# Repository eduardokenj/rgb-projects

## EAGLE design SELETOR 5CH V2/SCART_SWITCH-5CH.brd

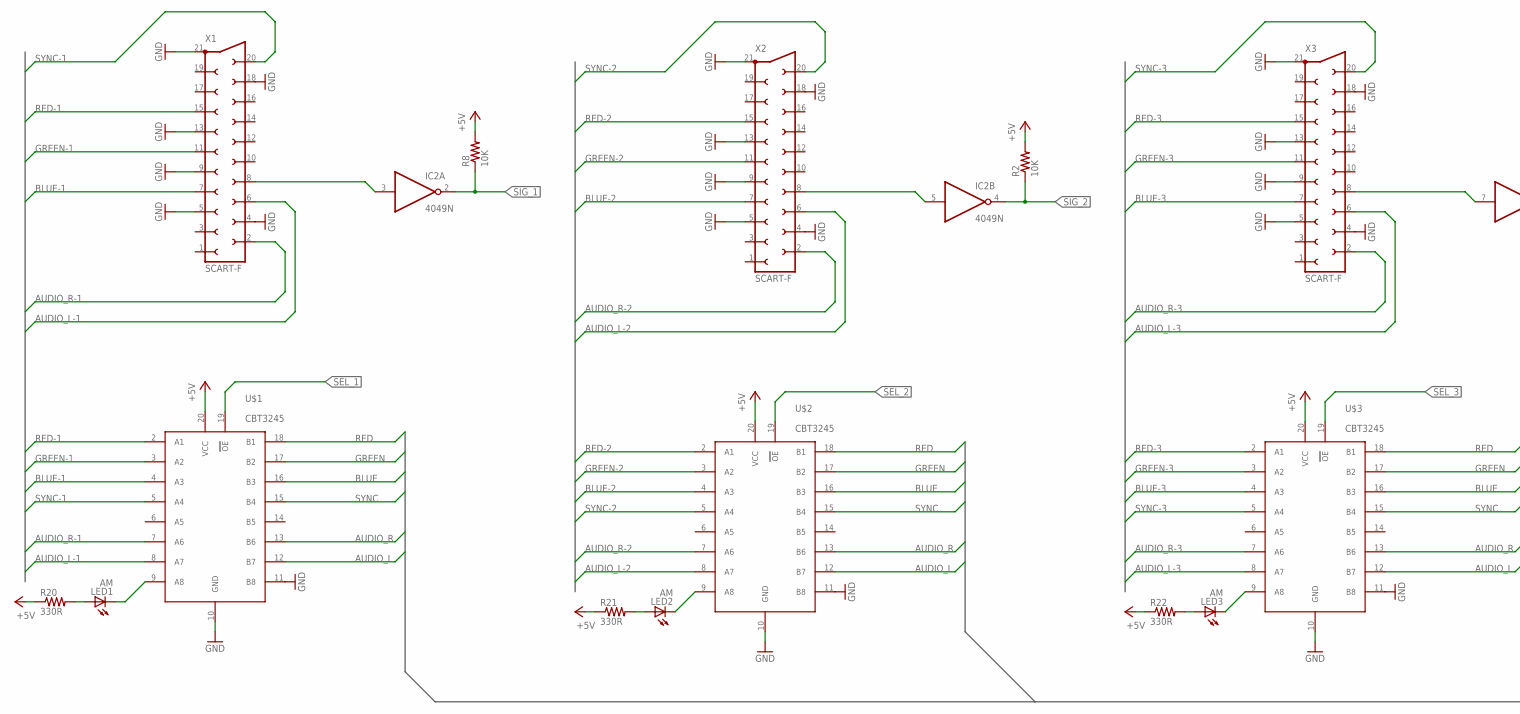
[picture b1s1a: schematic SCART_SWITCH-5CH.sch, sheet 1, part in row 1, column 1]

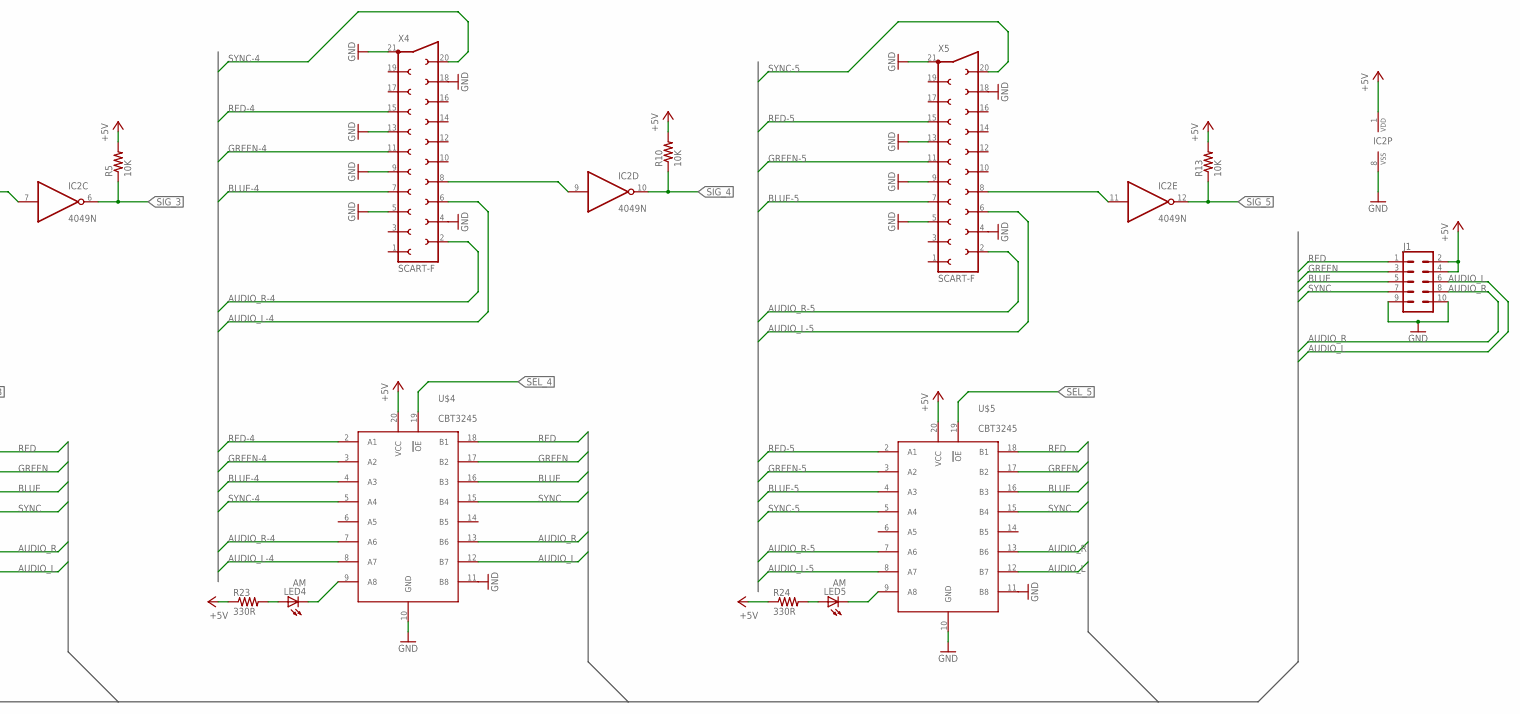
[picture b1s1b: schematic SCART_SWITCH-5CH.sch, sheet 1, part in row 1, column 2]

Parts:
IC2: 4049N; DIL16
J1: CONN_05X2SHD; 2X5-SHROUDED
LED1, LED2, LED3, LED4, LED5: AM; LED5MM
R2, R5, R8, R10, R13: 10K; 0204/7
R20, R21, R22, R23, R24: 330R; 0207/2V
U$1, U$2, U$3, U$4, U$5: CBT3245; SO20
X1, X2, X3, X4, X5: SCART-F

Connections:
+5V: IC2.1 (VDD), J1.2, J1.4, R2.2, R5.2, R8.2, R10.2, R13.2, R20.1, R21.1, R22.1, R23.1, R24.1, U$1.20 (VCC), U$2.20 (VCC), U$3.20 (VCC), U$4.20 (VCC), U$5.20 (VCC); also elsewhere on the board
AUDIO_L: J1.6, U$1.12 (B7), U$2.12 (B7), U$3.12 (B7), U$4.12 (B7), U$5.12 (B7)
AUDIO_L-1: U$1.8 (A7), X1.6
AUDIO_L-2: U$2.8 (A7), X2.6
AUDIO_L-3: U$3.8 (A7), X3.6
AUDIO_L-4: U$4.8 (A7), X4.6
AUDIO_L-5: U$5.8 (A7), X5.6
AUDIO_R: J1.8, U$1.13 (B6), U$2.13 (B6), U$3.13 (B6), U$4.13 (B6), U$5.13 (B6)
AUDIO_R-1: U$1.7 (A6), X1.2
AUDIO_R-2: U$2.7 (A6), X2.2
AUDIO_R-3: U$3.7 (A6), X3.2
AUDIO_R-4: U$4.7 (A6), X4.2
AUDIO_R-5: U$5.7 (A6), X5.2
BLUE: J1.5, U$1.16 (B3), U$2.16 (B3), U$3.16 (B3), U$4.16 (B3), U$5.16 (B3)
BLUE-1: U$1.4 (A3), X1.7
BLUE-2: U$2.4 (A3), X2.7
BLUE-3: U$3.4 (A3), X3.7
BLUE-4: U$4.4 (A3), X4.7
BLUE-5: U$5.4 (A3), X5.7
GND: IC2.8 (VSS), J1.9, J1.10, U$1.10 (GND), U$1.11 (B8), U$2.10 (GND), U$2.11 (B8), U$3.10 (GND), U$3.11 (B8), U$4.10 (GND), U$4.11 (B8), U$5.10 (GND), U$5.11 (B8), X1.4, X1.5, X1.9, X1.13, X1.18, X1.21, X2.4, X2.5, X2.9, X2.13, X2.18, X2.21, X3.4, X3.5, X3.9, X3.13, X3.18, X3.21, X4.4, X4.5, X4.9, X4.13, X4.18, X4.21, X5.4, X5.5, X5.9, X5.13, X5.18, X5.21; also elsewhere on the board
GREEN: J1.3, U$1.17 (B2), U$2.17 (B2), U$3.17 (B2), U$4.17 (B2), U$5.17 (B2)
GREEN-1: U$1.3 (A2), X1.11
GREEN-2: U$2.3 (A2), X2.11
GREEN-3: U$3.3 (A2), X3.11
GREEN-4: U$4.3 (A2), X4.11
GREEN-5: U$5.3 (A2), X5.11
unnamed: IC2.3 (I), X1.8
unnamed: IC2.5 (I), X2.8
unnamed: IC2.7 (I), X3.8
unnamed: IC2.9 (I), X4.8
unnamed: IC2.11 (I), X5.8
unnamed: LED5.K (C), U$5.9 (A8)
unnamed: LED5.A, R24.2
unnamed: LED4.A, R23.2
unnamed: LED4.K (C), U$4.9 (A8)
unnamed: LED2.K (C), U$2.9 (A8)
unnamed: LED2.A, R21.2
unnamed: LED3.K (C), U$3.9 (A8)
unnamed: LED3.A, R22.2
unnamed: LED1.A, R20.2
unnamed: LED1.K (C), U$1.9 (A8)
RED: J1.1, U$1.18 (B1), U$2.18 (B1), U$3.18 (B1), U$4.18 (B1), U$5.18 (B1)
RED-1: U$1.2 (A1), X1.15
RED-2: U$2.2 (A1), X2.15
RED-3: U$3.2 (A1), X3.15
RED-4: U$4.2 (A1), X4.15
RED-5: U$5.2 (A1), X5.15
SEL_1: U$1.19 (OE); also elsewhere on the board
SEL_2: U$2.19 (OE); also elsewhere on the board
SEL_3: U$3.19 (OE); also elsewhere on the board
SEL_4: U$4.19 (OE); also elsewhere on the board
SEL_5: U$5.19 (OE); also elsewhere on the board
SIG_1: IC2.2 (O), R8.1; also elsewhere on the board
SIG_2: IC2.4 (O), R2.1; also elsewhere on the board
SIG_3: IC2.6 (O), R5.1; also elsewhere on the board
SIG_4: IC2.10 (O), R10.1; also elsewhere on the board
SIG_5: IC2.12 (O), R13.1; also elsewhere on the board
SYNC: J1.7, U$1.15 (B4), U$2.15 (B4), U$3.15 (B4), U$4.15 (B4), U$5.15 (B4)
SYNC-1: U$1.5 (A4), X1.20
SYNC-2: U$2.5 (A4), X2.20
SYNC-3: U$3.5 (A4), X3.20
SYNC-4: U$4.5 (A4), X4.20
SYNC-5: U$5.5 (A4), X5.20

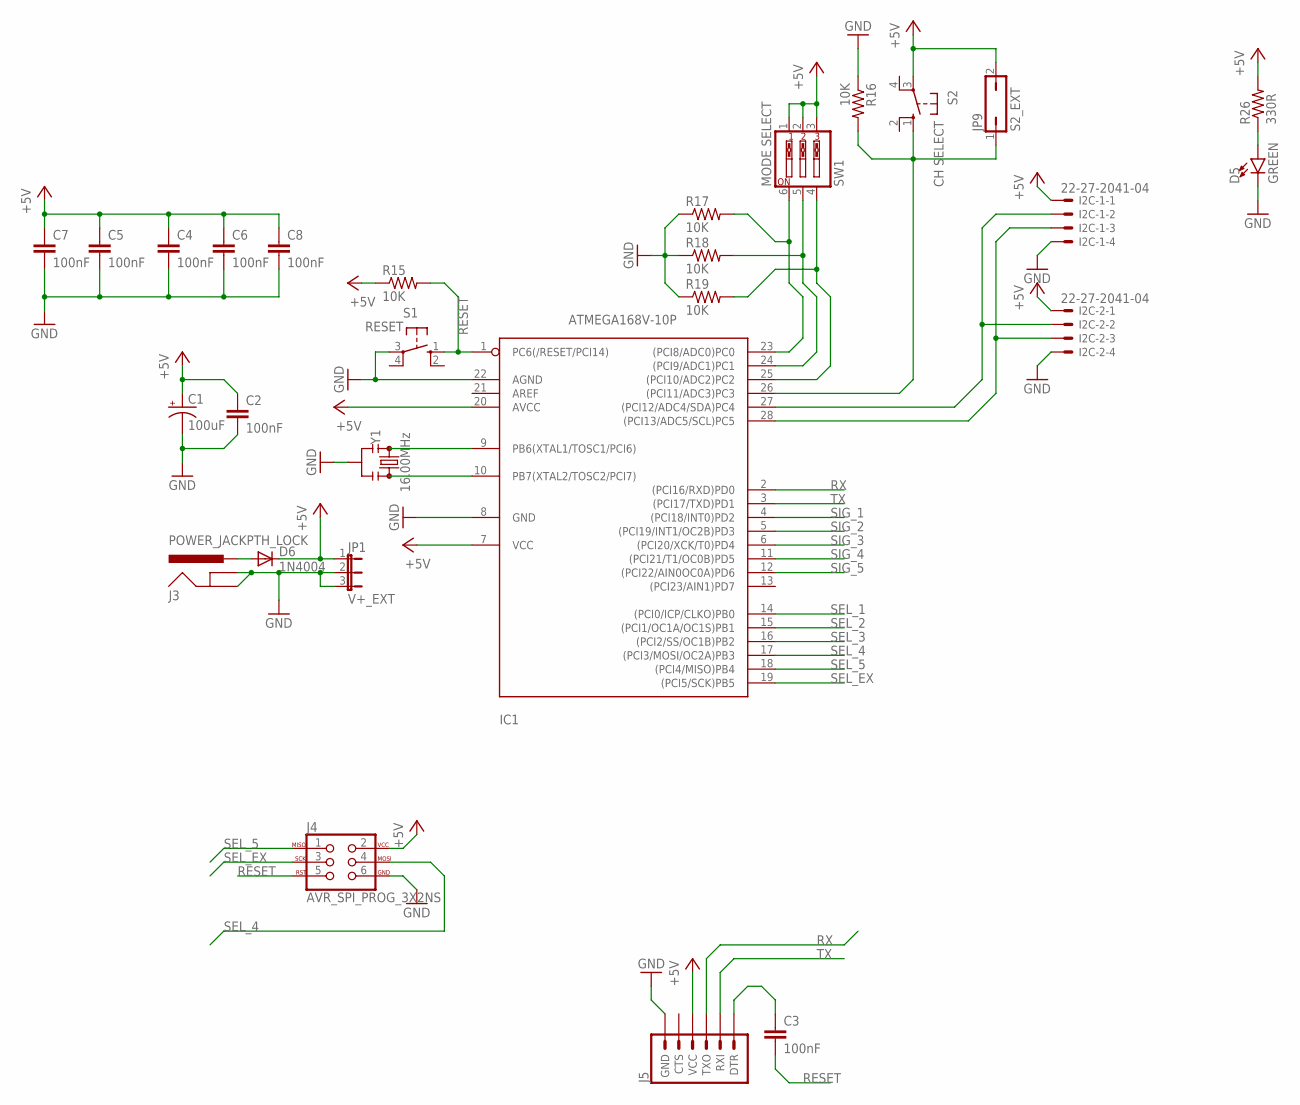
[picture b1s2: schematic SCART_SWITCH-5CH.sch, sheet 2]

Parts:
C1: 100uF; E2,5-7
C2, C3, C4, C5, C6, C7, C8: 100nF; C075-032X103
D5: GREEN; LED_5MM
D6: 1N4004; DO41-10
I2C-1, I2C-2: 22-27-2041-04; 6410-04
IC1: ATMEGA168V-10P; DIL28-3
J3: POWER_JACKPTH_LOCK; POWER_JACK_PTH_LOCK
J4: AVR_SPI_PROG_3X2NS; 2X3-NS
J5: 6_PIN_SERIAL_TARGETSILK; 6_PIN_SERIAL_TARGET_SIDE_W_SILK
JP1: V+_EXT; JP2
JP9: S2_EXT; JP1
R15, R16, R17, R18, R19: 10K; 0204/7
R26: 330R; 0204/7
S1: RESET; B3F-10XX
S2: CH SELECT; B3F-10XX
SW1: MODE SELECT; EDG-03
Y1: 16.00MHz; RESONATOR-PTH-7.6X3.8

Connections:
+5V: C1.+, C2.1, C4.1, C5.1, C6.1, C7.1, C8.1, D6.C, I2C-1.1, I2C-2.1, IC1.7 (VCC), IC1.20 (AVCC), J4.2, J5.P$4 (VCC), JP1.1, JP9.2, R15.1, R26.2, S2.3, SW1.1, SW1.2, SW1.3; also elsewhere on the board
GND: C1.-, C2.2, C4.2, C5.2, C6.2, C7.2, C8.2, D5.K (C), I2C-1.4, I2C-2.4, IC1.8 (GND), IC1.22 (AGND), J3.GND, J3.GNDBREAK, J4.6, J5.P$6 (GND), JP1.2, JP1.3, R16.1, R17.1, R18.1, R19.1, S1.3, Y1.2; also elsewhere on the board
unnamed: IC1.9 (PB6(XTAL1/TOSC1/PCI6)), Y1.1
unnamed: IC1.10 (PB7(XTAL2/TOSC2/PCI7)), Y1.3
unnamed: I2C-1.2, I2C-2.2, IC1.27 ((PCI12/ADC4/SDA)PC4)
unnamed: I2C-1.3, I2C-2.3, IC1.28 ((PCI13/ADC5/SCL)PC5)
unnamed: IC1.26 ((PCI11/ADC3)PC3), JP9.1, R16.2, S2.1 (S)
unnamed: IC1.23 ((PCI8/ADC0)PC0), R17.2, SW1.6
unnamed: IC1.24 ((PCI9/ADC1)PC1), R18.2, SW1.5
unnamed: IC1.25 ((PCI10/ADC2)PC2), R19.2, SW1.4
unnamed: C3.1, J5.P$1 (DTR)
unnamed: D5.A, R26.1
unnamed: D6.A, J3.PWR
RESET: C3.2, IC1.1 (PC6(/RESET/PCI14)), J4.5, R15.2, S1.1 (S)
RX: IC1.2 ((PCI16/RXD)PD0), J5.P$2 (TXO)
SEL_1: IC1.14 ((PCI0/ICP/CLKO)PB0); also elsewhere on the board
SEL_2: IC1.15 ((PCI1/OC1A/OC1S)PB1); also elsewhere on the board
SEL_3: IC1.16 ((PCI2/SS/OC1B)PB2); also elsewhere on the board
SEL_4: IC1.17 ((PCI3/MOSI/OC2A)PB3), J4.4; also elsewhere on the board
SEL_5: IC1.18 ((PCI4/MISO)PB4), J4.1; also elsewhere on the board
SEL_EX: IC1.19 ((PCI5/SCK)PB5), J4.3
SIG_1: IC1.4 ((PCI18/INT0)PD2); also elsewhere on the board
SIG_2: IC1.5 ((PCI19/INT1/OC2B)PD3); also elsewhere on the board
SIG_3: IC1.6 ((PCI20/XCK/T0)PD4); also elsewhere on the board
SIG_4: IC1.11 ((PCI21/T1/OC0B)PD5); also elsewhere on the board
SIG_5: IC1.12 ((PCI22/AIN0OC0A)PD6); also elsewhere on the board
TX: IC1.3 ((PCI17/TXD)PD1), J5.P$3 (RXI)

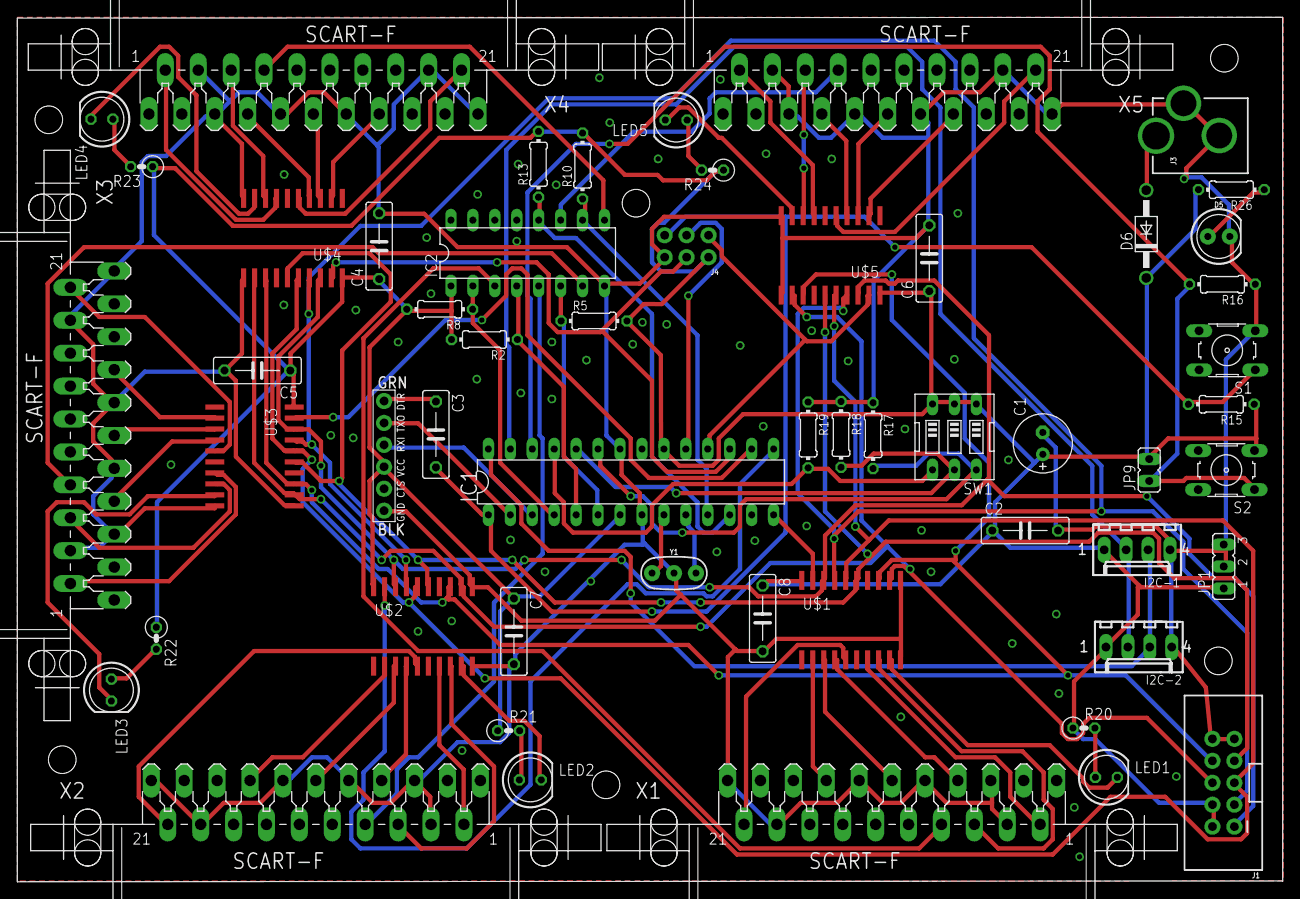
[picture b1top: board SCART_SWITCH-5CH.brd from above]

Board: 2 copper layers, 146.5 x 100.1 mm, 55 parts (0 on the bottom side), 78 nets.

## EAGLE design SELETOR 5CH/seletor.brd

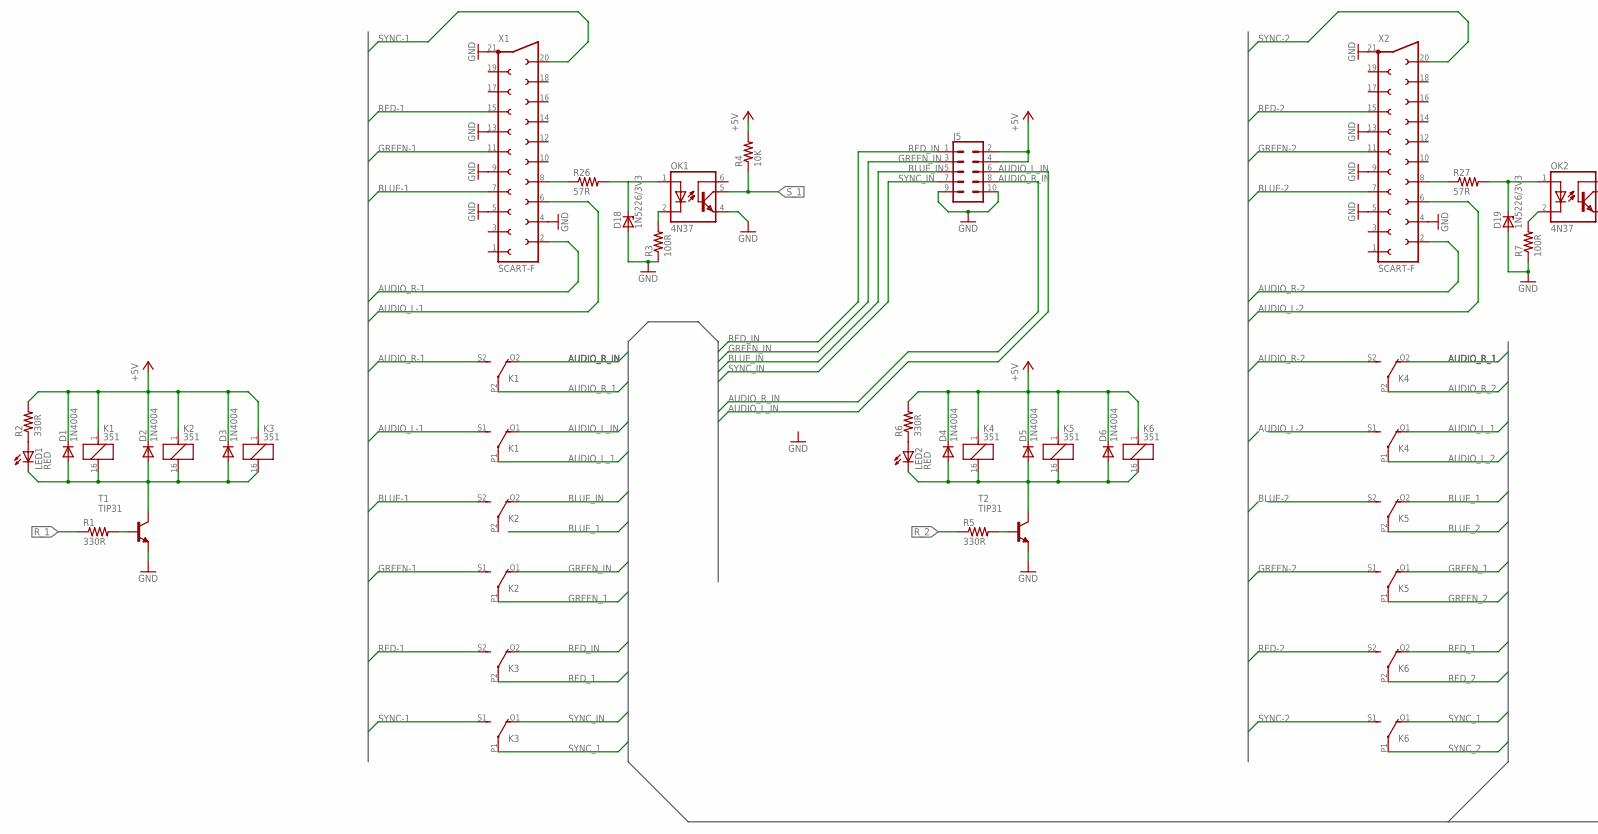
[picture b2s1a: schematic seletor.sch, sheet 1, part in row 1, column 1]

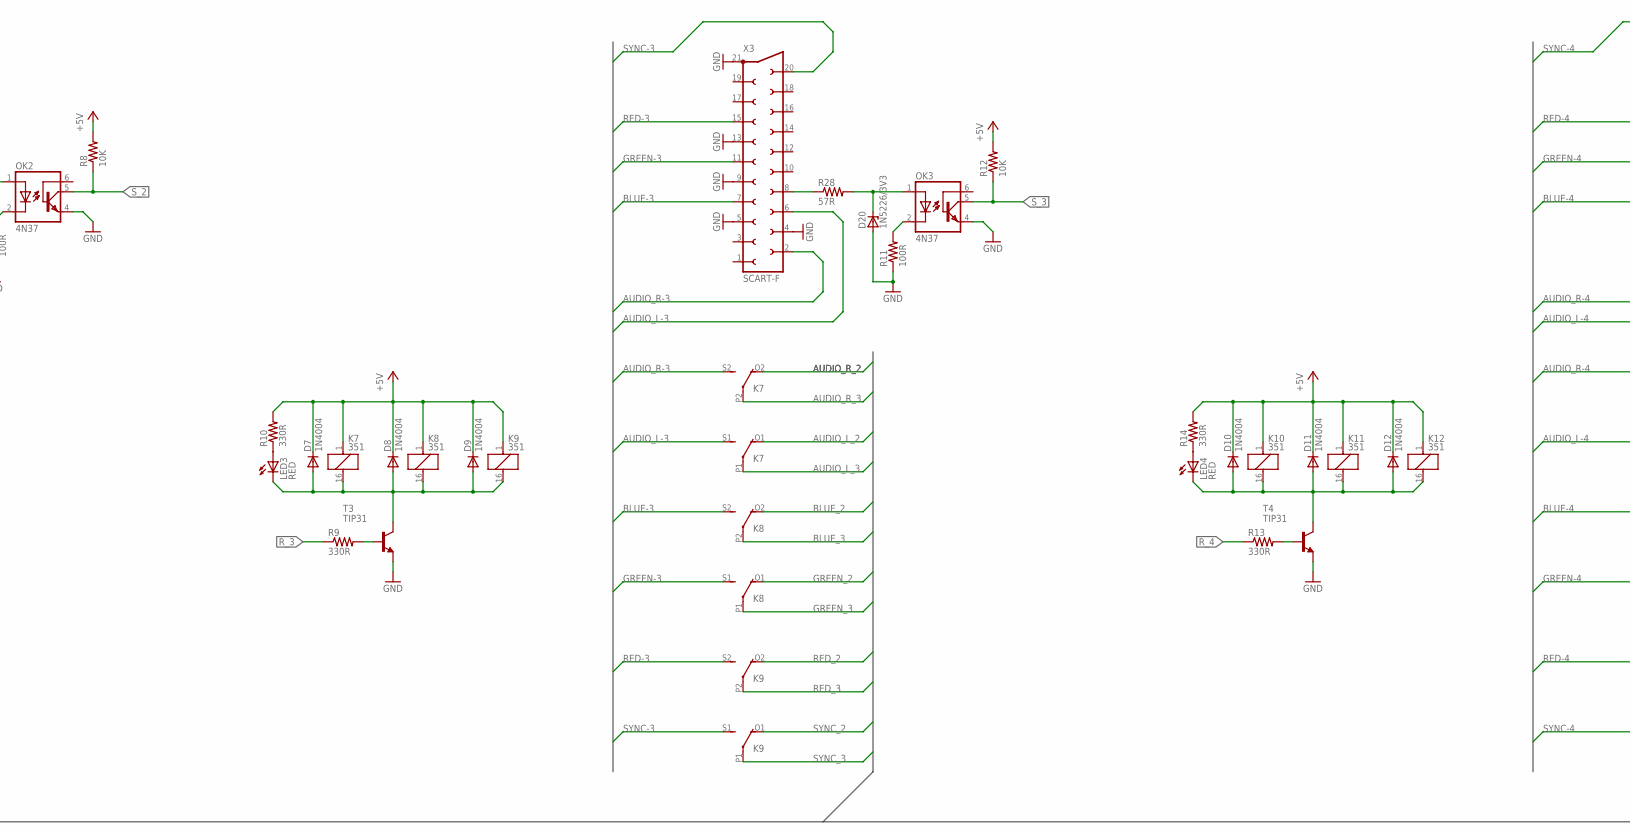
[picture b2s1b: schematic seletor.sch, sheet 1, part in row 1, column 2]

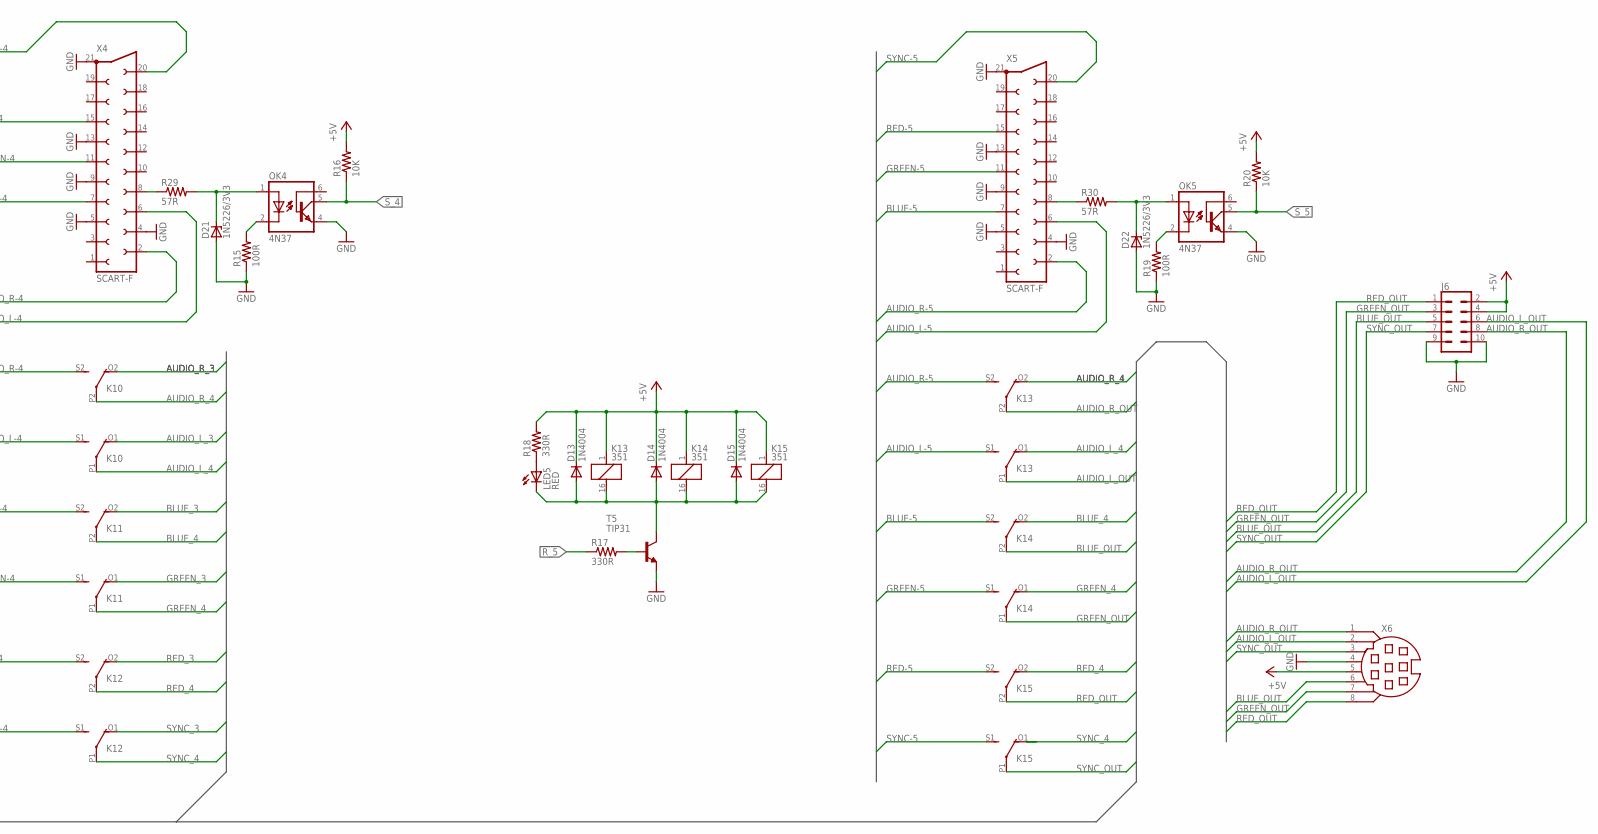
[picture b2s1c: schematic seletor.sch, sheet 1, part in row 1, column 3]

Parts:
D1, D2, D3, D4, D5, D6, D7, D8, D9, D10, D11, D12, D13, D14, D15: 1N4004; DO41-10
D18, D19, D20, D21, D22: 1N5226/3V3; DO34Z7
J5, J6: CONN_05X2SHD; 2X5-SHROUDED
K1, K2, K3, K4, K5, K6, K7, K8, K9, K10, K11, K12, K13, K14, K15: 351
LED1, LED2, LED3, LED4, LED5: RED; LED5MM
OK1, OK2, OK3, OK4, OK5: 4N37; DIL06
R1, R5, R9, R13, R17: 330R; 0204/7
R2, R6, R10, R14, R18: 330R; 0204V
R3, R7, R11, R15, R19: 100R; 0204V
R4, R8, R12, R16, R20: 10K; 0204V
R26, R27, R28, R29, R30: 57R; 0204/7
T1, T2, T3, T4, T5: TIP31; TO220
X1, X2, X3, X4, X5: SCART-F
X6: MD08SS; MDIN08SS

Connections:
+5V: D1.C, D2.C, D3.C, D4.C, D5.C, D6.C, D7.C, D8.C, D9.C, D10.C, D11.C, D12.C, D13.C, D14.C, D15.C, J5.2, J5.4, J6.2, J6.4, K1.1, K2.1, K3.1, K4.1, K5.1, K6.1, K7.1, K8.1, K9.1, K10.1, K11.1, K12.1, K13.1, K14.1, K15.1, R2.2, R4.2, R6.2, R8.2, R10.2, R12.2, R14.2, R16.2, R18.2, R20.2, X6.5; also elsewhere on the board
AUDIO_L-1: K1.S1 (S), X1.6
AUDIO_L-2: X2.6
AUDIO_L-3: K7.S1 (S), X3.6
AUDIO_L-4: K10.S1 (S), X4.6
AUDIO_L-5: K13.S1 (S), X5.6
AUDIO_L_1: K1.P1, K4.O1 (O)
AUDIO_L_2: K4.P1, K7.O1 (O)
AUDIO_L_3: K7.P1, K10.O1 (O)
AUDIO_L_4: K10.P1, K13.O1 (O)
AUDIO_L_IN: J5.6, K1.O1 (O)
AUDIO_L_OUT: J6.6, K13.P1, X6.2
AUDIO_R-1: K1.S2 (S), X1.2
AUDIO_R-2: K4.S2 (S), X2.2
AUDIO_R-3: K7.S2 (S), X3.2
AUDIO_R-4: K10.S2 (S), X4.2
AUDIO_R-5: K13.S2 (S), X5.2
AUDIO_R_1: K1.P2, K4.O2 (O)
AUDIO_R_2: K4.P2, K7.O2 (O)
AUDIO_R_3: K7.P2, K10.O2 (O)
AUDIO_R_4: K10.P2, K13.O2 (O)
AUDIO_R_IN: J5.8, K1.O2 (O)
AUDIO_R_OUT: J6.8, K13.P2, X6.1
BLUE-1: K2.S2 (S), X1.7
BLUE-2: X2.7
BLUE-3: K8.S2 (S), X3.7
BLUE-4: K11.S2 (S), X4.7
BLUE-5: K14.S2 (S), X5.7
BLUE_1: K5.O2 (O)
BLUE_2: K5.P2, K8.O2 (O)
BLUE_3: K8.P2, K11.O2 (O)
BLUE_4: K11.P2, K14.O2 (O)
BLUE_IN: J5.5, K2.O2 (O)
BLUE_OUT: J6.5, K14.P2, X6.6
GND: D18.A, D19.A, D20.A, D21.A, D22.A, J5.9, J5.10, J6.9, J6.10, OK1.4 (EMI), OK2.4 (EMI), OK3.4 (EMI), OK4.4 (EMI), OK5.4 (EMI), R3.1, R7.1, R11.1, R15.1, R19.1, T1.3 (E), T2.3 (E), T3.3 (E), T4.3 (E), T5.3 (E), X1.4, X1.5, X1.9, X1.13, X1.21, X2.4, X2.5, X2.9, X2.13, X2.21, X3.4, X3.5, X3.9, X3.13, X3.21, X4.4, X4.5, X4.9, X4.13, X4.21, X5.4, X5.5, X5.9, X5.13, X5.21, X6.4; also elsewhere on the board
GREEN-1: K2.S1 (S), X1.11
GREEN-2: K5.S1 (S), X2.11
GREEN-3: K8.S1 (S), X3.11
GREEN-4: K11.S1 (S), X4.11
GREEN-5: K14.S1 (S), X5.11
GREEN_1: K2.P1, K5.O1 (O)
GREEN_2: K5.P1, K8.O1 (O)
GREEN_3: K8.P1, K11.O1 (O)
GREEN_4: K11.P1, K14.O1 (O)
GREEN_IN: J5.3, K2.O1 (O)
GREEN_OUT: J6.3, K14.P1, X6.7
unnamed: D1.A, D2.A, D3.A, K1.16 (2), K2.16 (2), K3.16 (2), LED1.K (C), T1.2 (C)
unnamed: LED1.A, R2.1
unnamed: R26.1, X1.8
unnamed: OK1.2 (C), R3.2
unnamed: D4.A, D5.A, D6.A, K4.16 (2), K5.16 (2), K6.16 (2), LED2.K (C), T2.2 (C)
unnamed: R1.2, T1.1 (B)
unnamed: LED2.A, R6.1
unnamed: R5.2, T2.1 (B)
unnamed: R27.1, X2.8
unnamed: OK2.2 (C), R7.2
unnamed: D7.A, D8.A, D9.A, K7.16 (2), K8.16 (2), K9.16 (2), LED3.K (C), T3.2 (C)
unnamed: LED3.A, R10.1
unnamed: R9.2, T3.1 (B)
unnamed: R28.1, X3.8
unnamed: OK3.2 (C), R11.2
unnamed: D10.A, D11.A, D12.A, K10.16 (2), K11.16 (2), K12.16 (2), LED4.K (C), T4.2 (C)
unnamed: LED4.A, R14.1
unnamed: R13.2, T4.1 (B)
unnamed: R29.1, X4.8
unnamed: OK4.2 (C), R15.2
unnamed: D13.A, D14.A, D15.A, K13.16 (2), K14.16 (2), K15.16 (2), LED5.K (C), T5.2 (C)
unnamed: LED5.A, R18.1
unnamed: R17.2, T5.1 (B)
unnamed: R30.1, X5.8
unnamed: OK5.2 (C), R19.2
unnamed: D22.C, OK5.1 (A), R30.2
unnamed: D21.C, OK4.1 (A), R29.2
unnamed: D20.C, OK3.1 (A), R28.2
unnamed: D18.C, OK1.1 (A), R26.2
unnamed: D19.C, OK2.1 (A), R27.2
RED-1: K3.S2 (S), X1.15
RED-2: K6.S2 (S), X2.15
RED-3: K9.S2 (S), X3.15
RED-4: K12.S2 (S), X4.15
RED-5: K15.S2 (S), X5.15
RED_1: K3.P2, K6.O2 (O)
RED_2: K6.P2, K9.O2 (O)
RED_3: K9.P2, K12.O2 (O)
RED_4: K12.P2, K15.O2 (O)
RED_IN: J5.1, K3.O2 (O)
RED_OUT: J6.1, K15.P2, X6.8
R_1: R1.1; also elsewhere on the board
R_2: R5.1; also elsewhere on the board
R_3: R9.1; also elsewhere on the board
R_4: R13.1; also elsewhere on the board
R_5: R17.1; also elsewhere on the board
SYNC-1: K3.S1 (S), X1.20
SYNC-2: K6.S1 (S), X2.20
SYNC-3: K9.S1 (S), X3.20
SYNC-4: K12.S1 (S), X4.20
SYNC-5: K15.S1 (S), X5.20
SYNC_1: K3.P1, K6.O1 (O)
SYNC_2: K6.P1, K9.O1 (O)
SYNC_3: K9.P1, K12.O1 (O)
SYNC_4: K12.P1, K15.O1 (O)
SYNC_IN: J5.7, K3.O1 (O)
SYNC_OUT: J6.7, K15.P1, X6.3
S_1: OK1.5 (COL), R4.1; also elsewhere on the board
S_2: OK2.5 (COL), R8.1; also elsewhere on the board
S_3: OK3.5 (COL), R12.1; also elsewhere on the board
S_4: OK4.5 (COL), R16.1; also elsewhere on the board
S_5: OK5.5 (COL), R20.1; also elsewhere on the board

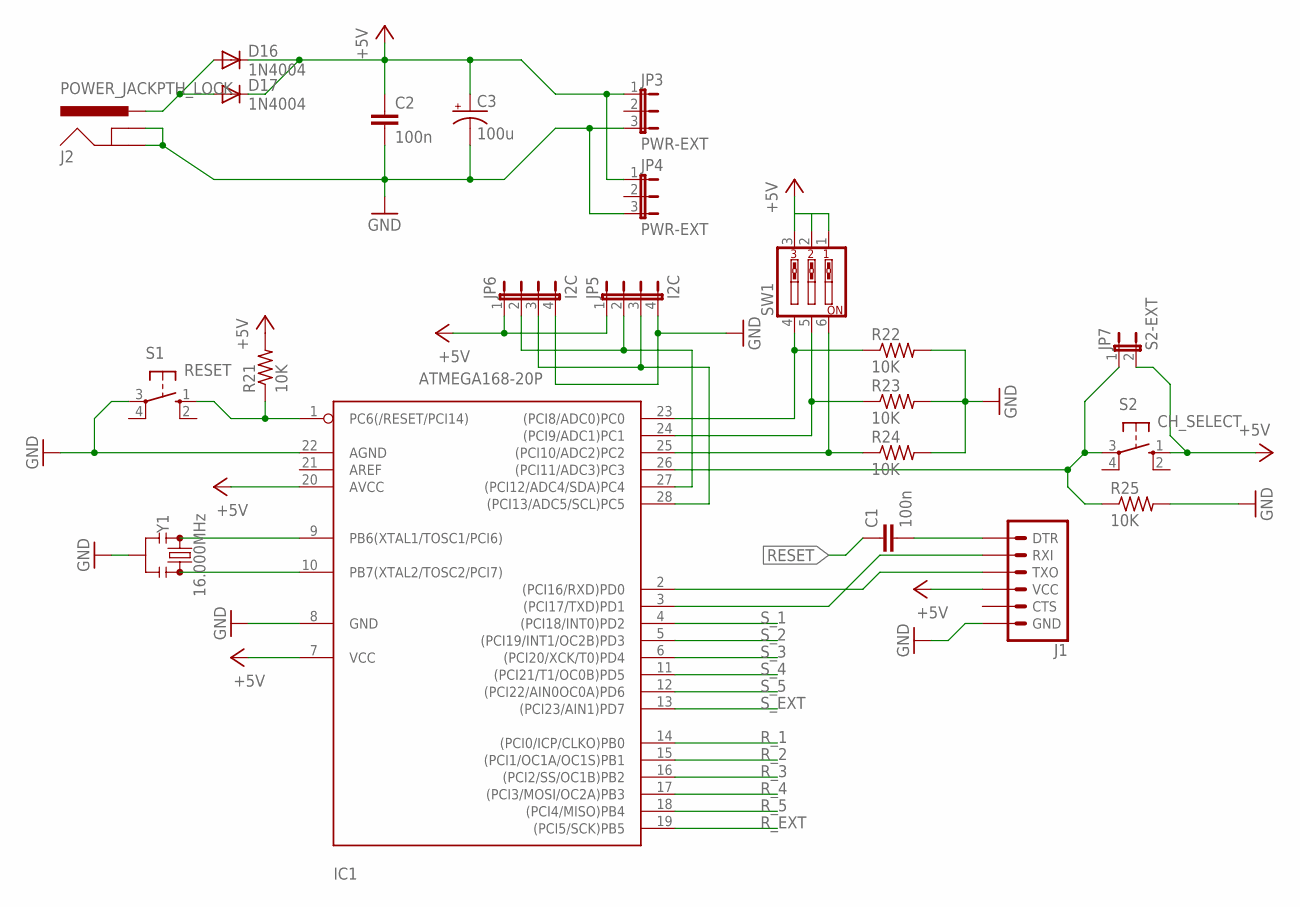
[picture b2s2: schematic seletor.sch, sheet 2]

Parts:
C1, C2: 100n; C7.5B3
C3: 100u; E3,5-10
D16, D17: 1N4004; DO41-10
IC1: ATMEGA168-20P; DIL28-3
J1: 6_PIN_SERIAL_TARGETSILK; 6_PIN_SERIAL_TARGET_SIDE_W_SILK
J2: POWER_JACKPTH_LOCK; POWER_JACK_PTH_LOCK
JP3, JP4: PWR-EXT; JP2
JP5, JP6: I2C; JP4
JP7: S2-EXT; JP1
R21, R22, R23, R24, R25: 10K; 0204/7
S1: RESET; B3F-10XX
S2: CH_SELECT; B3F-10XX
SW1: SW_DIP-3; EDG-03
Y1: 16.000MHz; RESONATOR-PTH-7.6X3.8

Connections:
+5V: C2.1, C3.+, D16.C, D17.C, IC1.7 (VCC), IC1.20 (AVCC), J1.P$4 (VCC), JP3.1, JP4.1, JP5.1, JP6.1, JP7.2, R21.2, S2.1 (S), SW1.1, SW1.2, SW1.3; also elsewhere on the board
GND: C2.2, C3.-, IC1.8 (GND), IC1.22 (AGND), J1.P$6 (GND), J2.GND, J2.GNDBREAK, JP3.3, JP4.3, JP5.4, JP6.4, R22.2, R23.2, R24.2, R25.2, S1.3, Y1.2; also elsewhere on the board
unnamed: IC1.2 ((PCI16/RXD)PD0), J1.P$2 (TXO)
unnamed: IC1.3 ((PCI17/TXD)PD1), J1.P$3 (RXI)
unnamed: D16.A, D17.A, J2.PWR
unnamed: C1.2, J1.P$1 (DTR)
unnamed: IC1.9 (PB6(XTAL1/TOSC1/PCI6)), Y1.1
unnamed: IC1.10 (PB7(XTAL2/TOSC2/PCI7)), Y1.3
unnamed: IC1.26 ((PCI11/ADC3)PC3), JP7.1, R25.1, S2.3
unnamed: IC1.25 ((PCI10/ADC2)PC2), R24.1, SW1.6
unnamed: IC1.24 ((PCI9/ADC1)PC1), R23.1, SW1.5
unnamed: IC1.23 ((PCI8/ADC0)PC0), R22.1, SW1.4
unnamed: IC1.27 ((PCI12/ADC4/SDA)PC4), JP5.2, JP6.2
unnamed: IC1.28 ((PCI13/ADC5/SCL)PC5), JP5.3, JP6.3
RESET: C1.1, IC1.1 (PC6(/RESET/PCI14)), R21.1, S1.1 (S)
R_1: IC1.14 ((PCI0/ICP/CLKO)PB0); also elsewhere on the board
R_2: IC1.15 ((PCI1/OC1A/OC1S)PB1); also elsewhere on the board
R_3: IC1.16 ((PCI2/SS/OC1B)PB2); also elsewhere on the board
R_4: IC1.17 ((PCI3/MOSI/OC2A)PB3); also elsewhere on the board
R_5: IC1.18 ((PCI4/MISO)PB4); also elsewhere on the board
R_EXT: IC1.19 ((PCI5/SCK)PB5)
S_1: IC1.4 ((PCI18/INT0)PD2); also elsewhere on the board
S_2: IC1.5 ((PCI19/INT1/OC2B)PD3); also elsewhere on the board
S_3: IC1.6 ((PCI20/XCK/T0)PD4); also elsewhere on the board
S_4: IC1.11 ((PCI21/T1/OC0B)PD5); also elsewhere on the board
S_5: IC1.12 ((PCI22/AIN0OC0A)PD6); also elsewhere on the board
S_EXT: IC1.13 ((PCI23/AIN1)PD7)

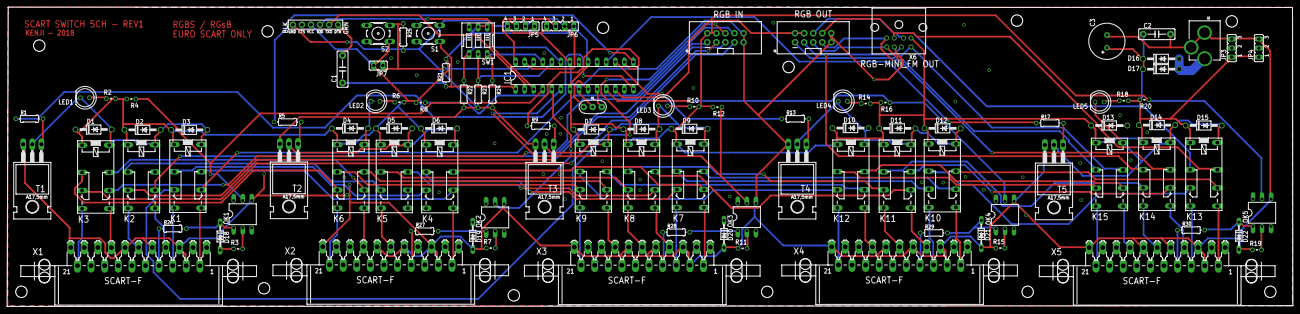
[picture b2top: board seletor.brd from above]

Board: 2 copper layers, 360.3 x 83.9 mm, 105 parts (0 on the bottom side), 118 nets.

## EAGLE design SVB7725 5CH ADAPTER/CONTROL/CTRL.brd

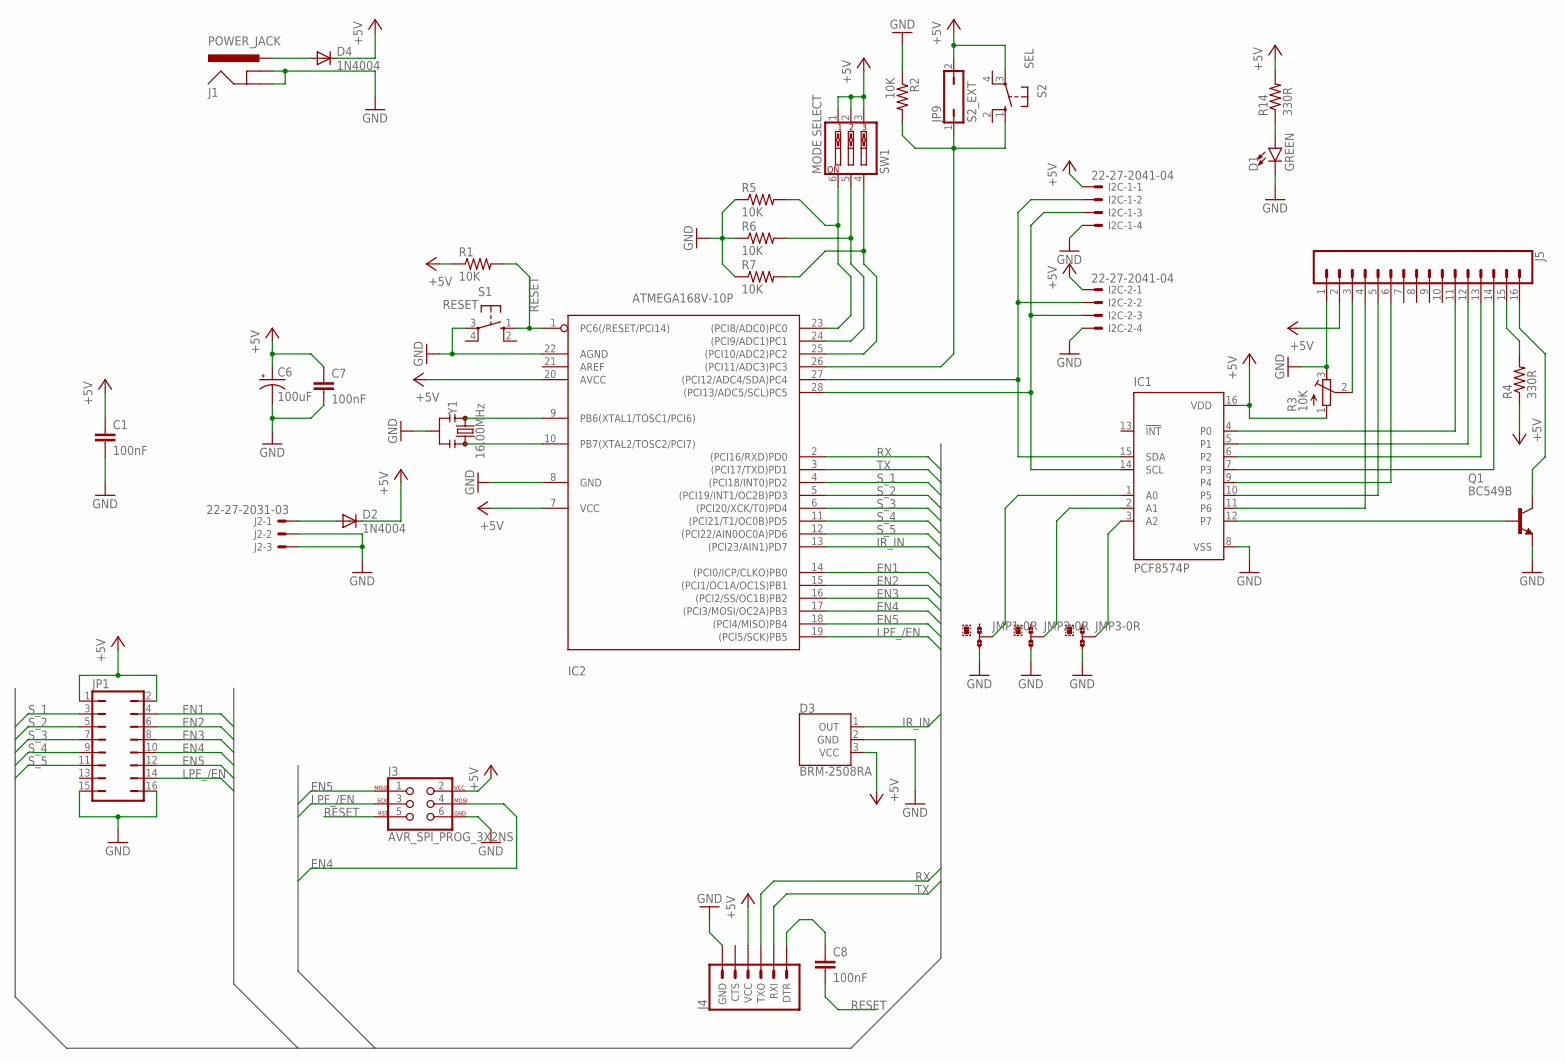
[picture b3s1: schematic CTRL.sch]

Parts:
C1, C7, C8: 100nF; C075-032X103
C6: 100uF; E2,5-7
D1: GREEN; LED_5MM
D2, D4: 1N4004; DO41-10
D3: BRM-2508RA; BRM-2508
I2C-1, I2C-2: 22-27-2041-04; 6410-04
IC1: PCF8574P; DIL16
IC2: ATMEGA168V-10P; DIL28-3
J1: POWER_JACK; POWER_JACK_PTH
J2: 22-27-2031-03; 6410-03
J3: AVR_SPI_PROG_3X2NS; 2X3-NS
J4: 6_PIN_SERIAL_TARGETSILK; 6_PIN_SERIAL_TARGET_SIDE_W_SILK
J5: CONN_16LONGPADS; 1X16_LONGPADS
JMP1, JMP2, JMP3: 0R-JUMPB; B0R-JMP
JP1: JP8Q
JP9: S2_EXT; JP1
Q1: BC549B; TO92-EBC
R1, R2, R5, R6, R7: 10K; 0204/7
R3: 10K; RTRIM3296P
R4, R14: 330R; 0204/7
S1: RESET; B3F-10XX
S2: SEL; B3F-10XX
SW1: MODE SELECT; EDG-03
Y1: 16.00MHz; RESONATOR-PTH-7.6X3.8

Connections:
+5V: C1.1, C6.+, C7.1, D2.C, D3.3 (VCC), D4.C, I2C-1.1, I2C-2.1, IC1.16 (VDD), IC2.7 (VCC), IC2.20 (AVCC), J3.2, J4.P$4 (VCC), J5.2, JP1.1, JP1.2, JP9.2, R1.1, R3.1 (A), R4.1, R14.2, S2.3, SW1.1, SW1.2, SW1.3
EN1: IC2.14 ((PCI0/ICP/CLKO)PB0), JP1.4
EN2: IC2.15 ((PCI1/OC1A/OC1S)PB1), JP1.6
EN3: IC2.16 ((PCI2/SS/OC1B)PB2), JP1.8
EN4: IC2.17 ((PCI3/MOSI/OC2A)PB3), J3.4, JP1.10
EN5: IC2.18 ((PCI4/MISO)PB4), J3.1, JP1.12
GND: C1.2, C6.-, C7.2, D1.K (C), D3.2 (GND), I2C-1.4, I2C-2.4, IC1.8 (VSS), IC2.8 (GND), IC2.22 (AGND), J1.GND, J1.GNDBREAK, J2.2, J2.3, J3.6, J4.P$6 (GND), J5.1, JMP1.3, JMP2.3, JMP3.3, JP1.15, JP1.16, Q1.E, R2.1, R3.3 (E), R5.1, R6.1, R7.1, S1.3, Y1.2
IR_IN: D3.1 (OUT), IC2.13 ((PCI23/AIN1)PD7)
LPF_/EN: IC2.19 ((PCI5/SCK)PB5), J3.3, JP1.14
unnamed: IC2.9 (PB6(XTAL1/TOSC1/PCI6)), Y1.1
unnamed: IC2.10 (PB7(XTAL2/TOSC2/PCI7)), Y1.3
unnamed: IC1.1 (A0), JMP1.2
unnamed: IC1.2 (A1), JMP2.2
unnamed: D4.A, J1.PWR
unnamed: IC1.3 (A2), JMP3.2
unnamed: I2C-1.2, I2C-2.2, IC1.15 (SDA), IC2.27 ((PCI12/ADC4/SDA)PC4)
unnamed: I2C-1.3, I2C-2.3, IC1.14 (SCL), IC2.28 ((PCI13/ADC5/SCL)PC5)
unnamed: IC2.26 ((PCI11/ADC3)PC3), JP9.1, R2.2, S2.1 (S)
unnamed: IC2.23 ((PCI8/ADC0)PC0), R5.2, SW1.6
unnamed: IC2.24 ((PCI9/ADC1)PC1), R6.2, SW1.5
unnamed: IC2.25 ((PCI10/ADC2)PC2), R7.2, SW1.4
unnamed: C8.1, J4.P$1 (DTR)
unnamed: D1.A, R14.1
unnamed: D2.A, J2.1
unnamed: IC1.4 (P0), J5.11
unnamed: IC1.5 (P1), J5.12
unnamed: IC1.6 (P2), J5.13
unnamed: IC1.7 (P3), J5.14
unnamed: IC1.9 (P4), J5.6
unnamed: IC1.10 (P5), J5.5
unnamed: IC1.11 (P6), J5.4
unnamed: J5.3, R3.2 (S)
unnamed: IC1.12 (P7), Q1.B
unnamed: J5.16, Q1.C
unnamed: J5.15, R4.2
RESET: C8.2, IC2.1 (PC6(/RESET/PCI14)), J3.5, R1.2, S1.1 (S)
RX: IC2.2 ((PCI16/RXD)PD0), J4.P$2 (TXO)
S_1: IC2.4 ((PCI18/INT0)PD2), JP1.3
S_2: IC2.5 ((PCI19/INT1/OC2B)PD3), JP1.5
S_3: IC2.6 ((PCI20/XCK/T0)PD4), JP1.7
S_4: IC2.11 ((PCI21/T1/OC0B)PD5), JP1.9
S_5: IC2.12 ((PCI22/AIN0OC0A)PD6), JP1.11
TX: IC2.3 ((PCI17/TXD)PD1), J4.P$3 (RXI)

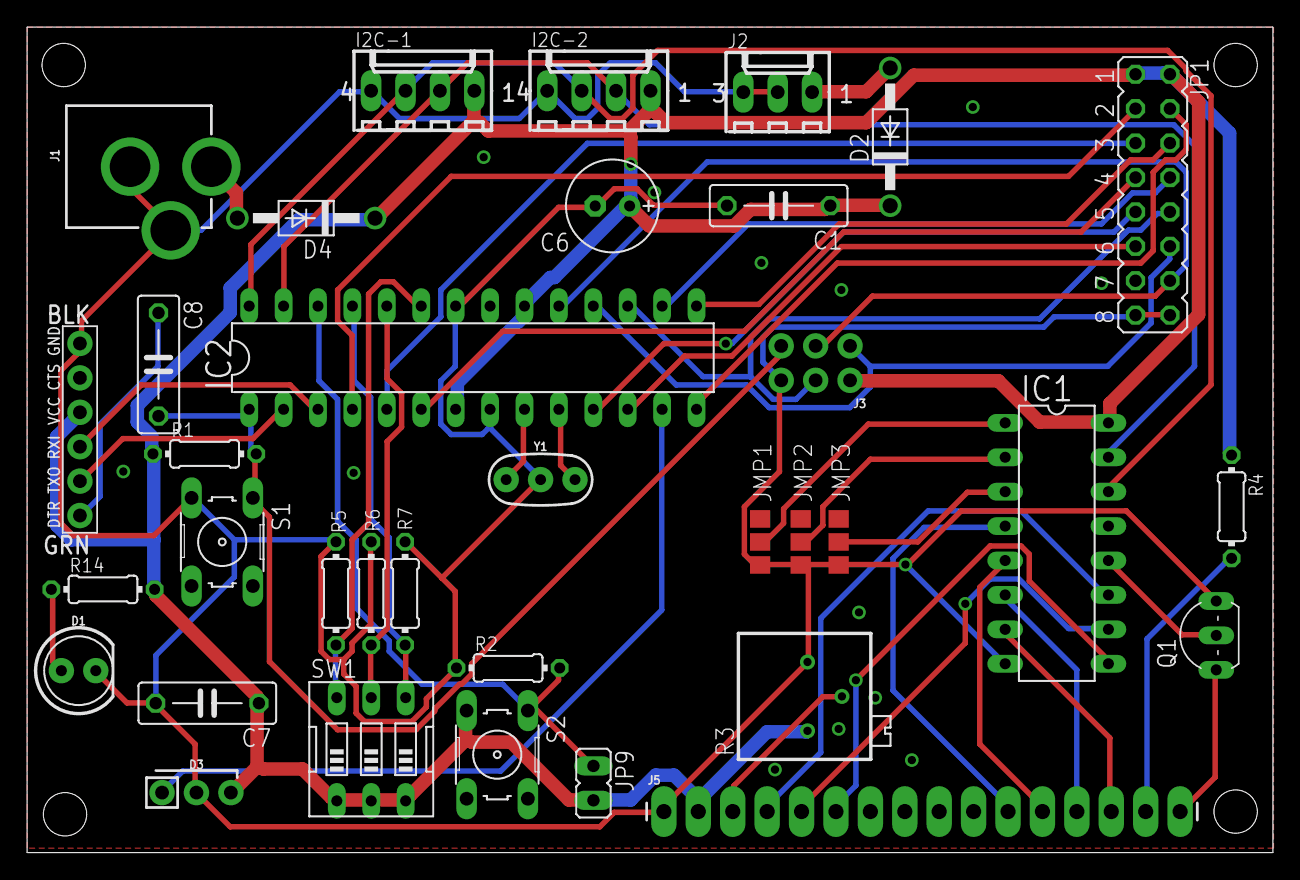
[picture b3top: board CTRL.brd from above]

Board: 2 copper layers, 91.9 x 60.9 mm, 35 parts (0 on the bottom side), 43 nets.

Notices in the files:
parts and their libraries:
SparkFun-LED: Licensing: Creative Commons ShareAlike 4.0 International - https://creativecommons.org/licenses/by-sa/4.0
